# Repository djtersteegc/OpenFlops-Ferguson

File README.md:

This is a respin of [SukkoPera's](https://github.com/SukkoPera) original [OpenFlops](https://github.com/SukkoPera/OpenFlops) project to create a custom version that plugs directly into the male 50 pin disk header of my [Ferguson Big Board](https://github.com/djtersteegc/Ferguson-Big-Board-Reproduction) SBC Z80 computer.  Changes from the original version include:

- Updated to KiCad 7.x
- Switched from USB to Micro SD for image storage
- Switched to 74LS07's for buffers
- Interface is a now a 50 pin connector and PCB laid out specifically for the Ferguson use case

Version 1.1 shrinks the SWD pin headers to allow room for a 9mm speaker to make floppy'ish sounds when accessing and seeking.

https://youtu.be/Bbqj_xtnAqc

Schematic v1.0 - https://djtersteegc.github.io/OpenFlops-Ferguson/OpenFlops-Ferguson-Schematic-v1.0.pdf

Schematic v1.1 - https://djtersteegc.github.io/OpenFlops-Ferguson/OpenFlops-Ferguson-Schematic-v1.1.pdf

### BOM

Interactive v1.0 - [https://djtersteegc.github.io/OpenFlops-Ferguson/ibom-v1.0.html](https://djtersteegc.github.io/OpenFlops-Ferguson/ibom-v1.0.html)

CSV v1.0 - [https://djtersteegc.github.io/OpenFlops-Ferguson/OpenFlops-Ferguson-BOM-v1.0.csv](https://djtersteegc.github.io/OpenFlops-Ferguson/OpenFlops-Ferguson-BOM-v1.0.csv)

Interactive v1.1 - [https://djtersteegc.github.io/OpenFlops-Ferguson/ibom-v1.1.html](https://djtersteegc.github.io/OpenFlops-Ferguson/ibom-v1.1.html)

CSV v1.1 - [https://djtersteegc.github.io/OpenFlops-Ferguson/OpenFlops-Ferguson-BOM-v1.1.csv](https://djtersteegc.github.io/OpenFlops-Ferguson/OpenFlops-Ferguson-BOM-v1.1.csv)

For the MCU I switched from the STM32F105RBT6 to the Artery AT32F435RGT7 which is now well supported by FlashFloppy and a more capable chip for potential future expansion (dual drives?). You could also build with the STM32F105RBT6 and use the appropiate STM programmer and FlashFloppy firmware version.

C12 is a extra bulk capacitor footprint I added near the MCU in case it was needed.  I've run mine without and seems fine, so can be considered optional.  Measured current draw on the board is around 100ma, with the OLED display active.

### Assembly

Do all the SMD components first using your favorite method.  I tried the Proto-Advantage PA0096-S TQFP-64 stencil for the MCU since I didn't have another one anywhere and was to cheap to get a proper stencil from JLCPCB, but unfortunately the pads are 2mm in length on that guy which result in excessive solder paste being applied to the board and then general sadness and bridging after it reflows.

I would flash the MCU (see below) next either by soldering on the angle headers for the SWD port or just holding headers in the holes to ensure everything works before doing the rest of the through hole components since it's a whole lot easier to do rework if needed with nothing else on the board.

Once all flashed and assembled, the normal jumper settings for the BOOT0 and BOOT1 pins are to the left (connected to GND).  BOOT1 really isn't even needed, but I added it just in case.

### Firmware Flashing

To flash the FlashFloppy firmware on the MCU, I used Arterty's AT-Link+ hooked up the SWD port on the board.

For the v1.1 boards, a pogo pin clamp is handy.

If your MCU is blank, you should be able to connect without having to set the BOOT0 jumper to high (3.3V)  If not and it is already running a user flashed program, you will need to move BOOT0 to the right in order for the bootloader to run and you can connect for flashing.

Using Artery's ICP Programmer, **Connect** to the MCU and load the appropiate FlashFloppy hex file via the **Add** button and then hit **DownLoad**.

Move the BOOT0 jumper back to the left (GND, logical 0) if needed and once you repower, the OLED should display FlashFloppy+. 

### Usage

If you have v1.0 repoduction board (or original), you will need to add a bodge wire to pull 5V power from the resistor network to either pin 4, 6, or 8 (or all three) since the FlashFloppy board is powered directly from normally unused pins on the Ferguson's floppy port.

If you have a version 1.1 board, simply close the solder jumper on the back of the board to do the same.

Plug into your Ferguson and enjoy a clutter free floppy experience. ;)

### Versions

**v1.0** - Initial release, tested and working.

**v1.1** - Shrinks the SWD pin headers to allow room for a 9mm speaker.

### Getting a Board

If you're in the US, hit me up on this VCFed thread and if I have any extras, can drop one in the mail for a couple bucks.  

https://forum.vcfed.org/index.php?threads/recreating-the-ferguson-big-board.68349/

Otherwise [gerbers](gerbers) are available for use at your favorite PCB fab. 

### License

The OpenFlops documentation, including the design itself, is copyright &copy; SukkoPera 2019-2020.

OpenFlops is Open Hardware licensed under the [CERN OHL v. 1.2](http://ohwr.org/cernohl).

You may redistribute and modify this documentation under the terms of the CERN OHL v.1.2. This documentation is distributed *as is* and WITHOUT ANY EXPRESS OR IMPLIED WARRANTIES whatsoever with respect to its functionality, operability or use, including, without limitation, any implied warranties OF MERCHANTABILITY, SATISFACTORY QUALITY, FITNESS FOR A PARTICULAR PURPOSE or infringement. We expressly disclaim any liability whatsoever for any direct, indirect, consequential, incidental or special damages, including, without limitation, lost revenues, lost profits, losses resulting from business interruption or loss of data, regardless of the form of action or legal theory under which the liability may be asserted, even if advised of the possibility or likelihood of such damages.

A copy of the full license is included in file [LICENSE.pdf](LICENSE.pdf), please refer to it for applicable conditions. In order to properly deal with its terms, please see file [LICENSE_HOWTO.pdf](LICENSE_HOWTO.pdf).

The contact points for information about manufactured Products (see section 4.2) are listed in file [PRODUCT.md](PRODUCT.md).

Any modifications made by Licensees (see section 3.4.b) shall be recorded in file [CHANGES.md](CHANGES.md).

The Documentation Location of the original project is https://github.com/SukkoPera/OpenFlops/.

### Thanks
- SukkoPera for the [OpenFlops](https://github.com/SukkoPera/OpenFlops) project
- H.M for publishing the [original Gotek schematics](docs/gotek_usb-fde_block-diagram.jpg)
- [keirf](https://github.com/keirf) for FlashFloppy

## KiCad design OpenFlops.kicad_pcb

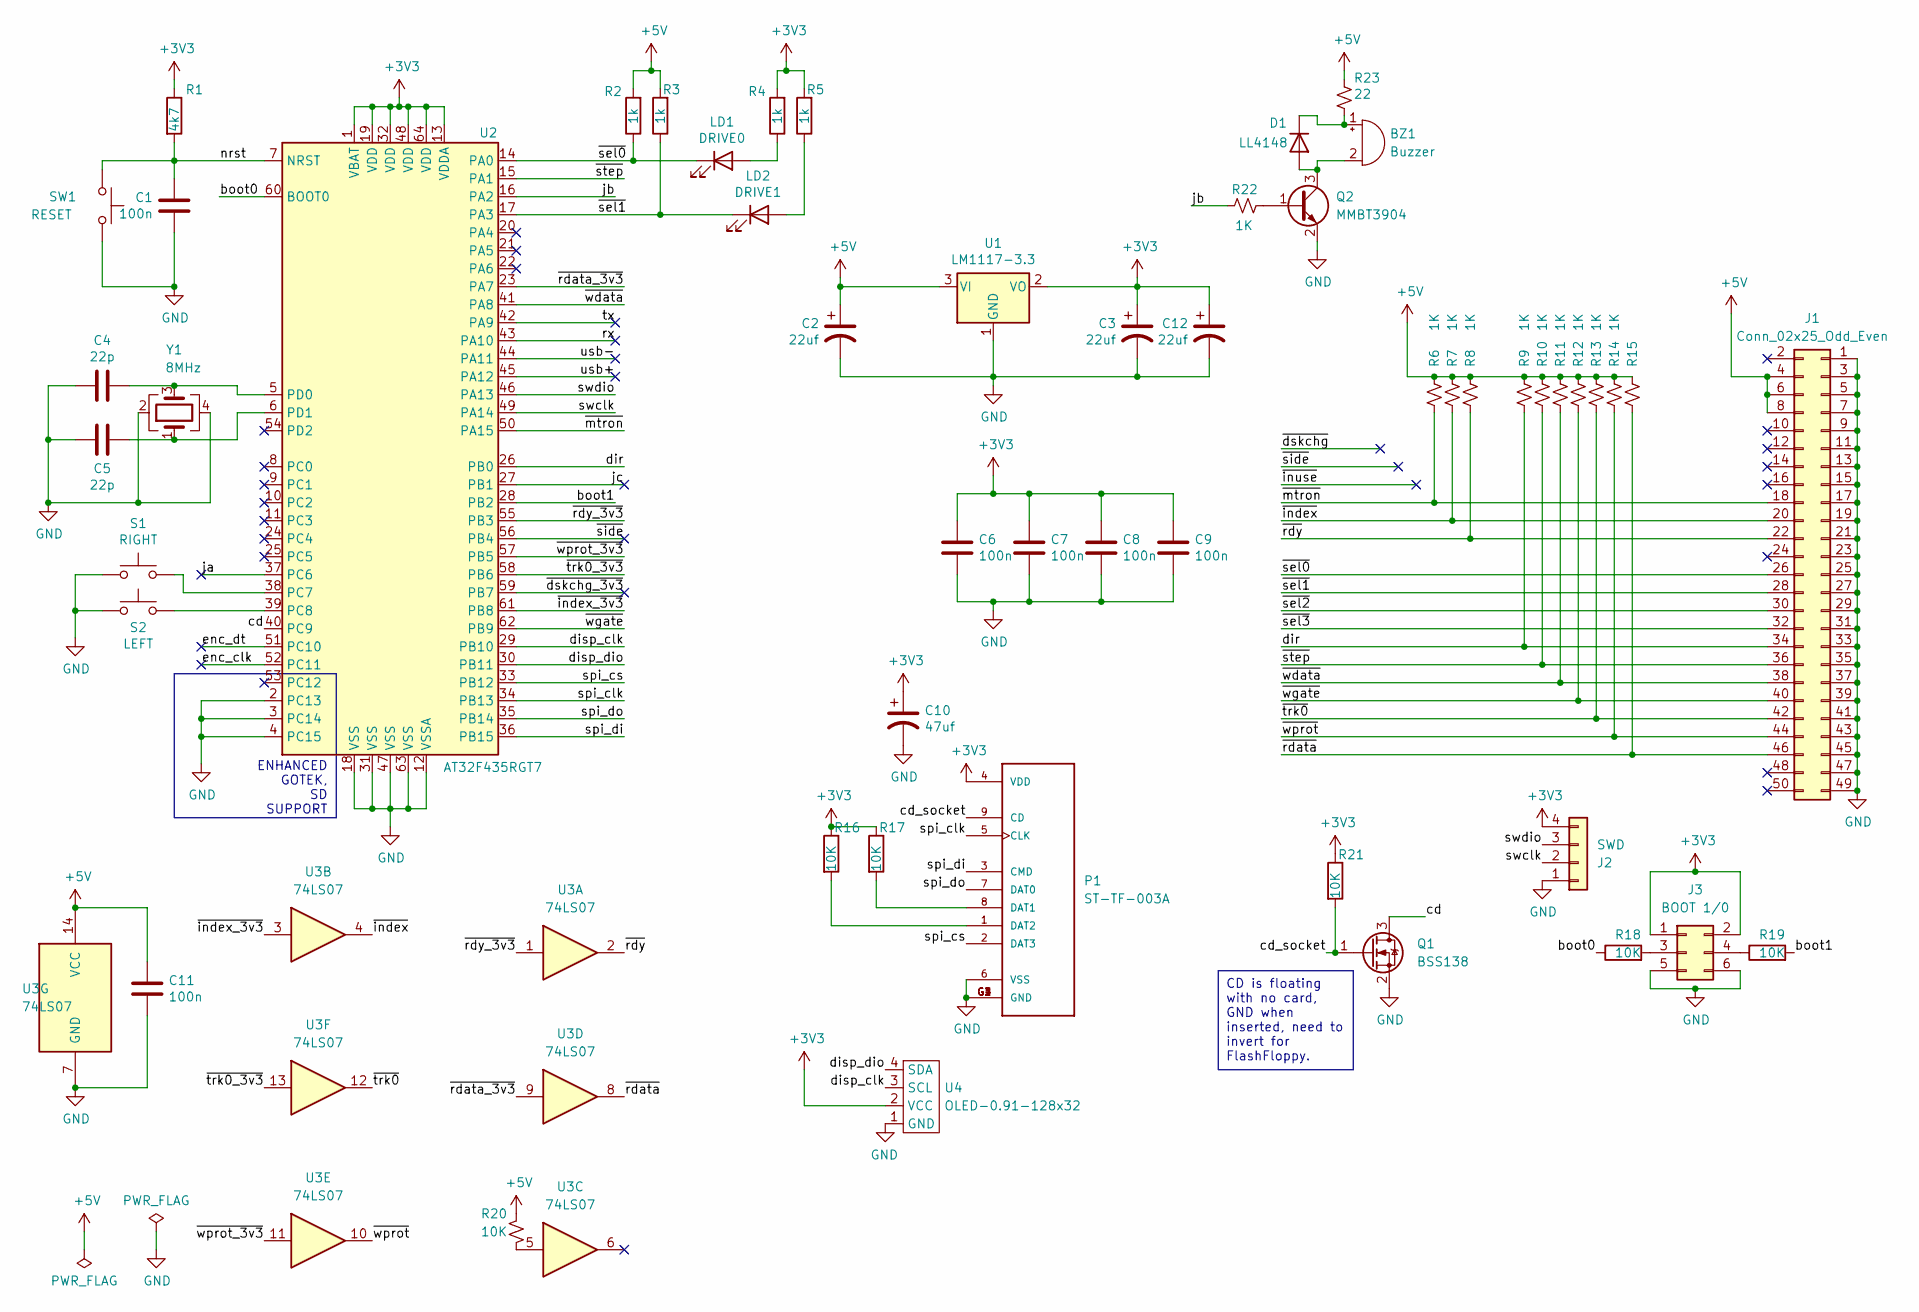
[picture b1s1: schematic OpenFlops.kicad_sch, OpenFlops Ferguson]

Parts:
BZ1: Buzzer; MagneticBuzzer_PUI_AT-0927-TT-6-R
C1, C6, C7, C8, C9, C11: 100n; C_0805_2012Metric; MFG Part Num MULTILAYER CERAMIC CAPACITORS MLCC - SM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; JLCPCB PN CC0805KRX7R9BB104
C2, C3, C12: 22uf; CP_EIA-3216-12_Kemet-S_Pad1.58x1.35mm_HandSolder
C4, C5: 22p; C_0805_2012Metric; MFG Part Num MULTILAYER CERAMIC CAPACITORS MLCC - SM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; JLCPCB PN CL21C220JBANNNC
C10: 47uf; CP_EIA-3528-12_Kemet-T_Pad1.50x2.35mm_HandSolder
D1: LL4148; D_MiniMELF
J1: Conn_02x25_Odd_Even; PinSocket_2x25_P2.54mm_Vertical
J2: SWD; PinHeader_1x04_P2.54mm_Vertical
J3: BOOT 1/0; PinHeader_2x03_P2.00mm_Vertical
LD1: DRIVE0; LED_D3.0mm
LD2: DRIVE1; LED_D3.0mm
P1: ST-TF-003A; SUNTECH_ST-TF-003A
Q1: BSS138; SOT-23
Q2: MMBT3904; SOT-23
R1: 4k7; R_0805_2012Metric; MFG Part Num CHIP RESISTOR - SURFACE MOUNT 4.7KOHMS 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; JLCPCB PN 0805W8F4701T5E
R2, R3: 1k; R_0805_2012Metric; MFG Part Num CHIP RESISTOR - SURFACE MOUNT 1KOHMS ±1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; JLCPCB PN 0805W8F1001T5E
R4, R5: 1k; R_0805_2012Metric
R6, R7, R8, R9, R10, R11, R12, R13, R14, R15, R22: 1K; R_0805_2012Metric
R16, R17, R18, R19, R21: 10K; R_0805_2012Metric; MFG Part Num CHIP RESISTOR - SURFACE MOUNT 4.7KOHMS 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; JLCPCB PN 0805W8F4701T5E
R20: 10K; R_0805_2012Metric
R23: 22; R_0805_2012Metric
S1: RIGHT; PUSH_BUTTON_RIGHT_ANGLE
S2: LEFT; PUSH_BUTTON_RIGHT_ANGLE
SW1: RESET; SW_Push_SPST_NO_Alps_SKRK
U1: LM1117-3.3; SOT-223-3_TabPin2; MFG Part Num LOW DROPOUT REGULATORS(LDO) POSITIVE FI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; JLCPCB PN AMS1117-3.3
U2: AT32F435RGT7; LQFP-64_10x10mm_P0.5mm; MFG Part Num ST MICROELECTRONICS LQFP-64_10X10X05P R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; JLCPCB PN STM32F105RBT6
U3: 74LS07; SOIC-14_3.9x8.7mm_P1.27mm
U4: OLED-0.91-128x32
Y1: 8MHz; Crystal_SMD_Abracon_ABM8G-4Pin_3.2x2.5mm

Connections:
+3V3: C3.1, C6.1, C7.1, C8.1, C9.1, C10.1, C12.1, J2.4, J3.1, J3.2, P1.4 (VDD), R1.1, R4.2, R5.2, R16.1, R17.1, R21.1, U1.2 (VO), U2.1 (VBAT), U2.13 (VDDA), U2.19 (VDD), U2.32 (VDD), U2.48 (VDD), U2.64 (VDD), U4.2 (VCC)
+5V: C2.1, C11.1, J1.4, J1.6, J1.8, R2.2, R3.2, R6.1, R7.1, R8.1, R9.1, R10.1, R11.1, R12.1, R13.1, R14.1, R15.1, R20.1, R23.1, U1.3 (VI), U3.14 (VCC)
/boot0: R18.1, U2.60 (BOOT0)
/boot1: R19.2, U2.28 (PB2)
/cd: Q1.3 (D), U2.40 (PC9)
/cd_socket: P1.9 (CD), Q1.1 (G), R21.2
/dir: J1.34, R9.2, U2.26 (PB0)
/disp_clk: U2.29 (PB10), U4.3 (SCL)
/disp_dio: U2.30 (PB11), U4.4 (SDA)
/enc_clk: U2.52 (PC11)
/enc_dt: U2.51 (PC10)
/ja: U2.37 (PC6)
/jb: R22.2, U2.16 (PA2)
/jc: U2.27 (PB1)
/nrst: C1.1, R1.2, SW1.1, U2.7 (NRST)
/rx: U2.43 (PA10)
/spi_clk: P1.5 (CLK), U2.34 (PB13)
/spi_cs: P1.2 (DAT3), U2.33 (PB12)
/spi_di: P1.3 (CMD), U2.36 (PB15)
/spi_do: P1.7 (DAT0), U2.35 (PB14)
/swclk: J2.2, U2.49 (PA14)
/swdio: J2.3, U2.46 (PA13)
/tx: U2.42 (PA9)
/usb+: U2.45 (PA12)
/usb-: U2.44 (PA11)
/~dskchg_3v3: U2.59 (PB7)
/~index_3v3: U2.61 (PB8), U3.3
/~index: J1.20, R7.2, U3.4
/~mtron: J1.18, R6.2, U2.50 (PA15)
/~rdata_3v3: U2.23 (PA7), U3.9
/~rdata: J1.46, R15.2, U3.8
/~rdy_3v3: U2.55 (PB3), U3.1
/~rdy: J1.22, R8.2, U3.2
/~sel0: J1.26, LD1.1 (K), R2.1, U2.14 (PA0)
/~sel1: J1.28, LD2.1 (K), R3.1, U2.17 (PA3)
/~sel2: J1.30
/~sel3: J1.32
/~side: U2.56 (PB4)
/~step: J1.36, R10.2, U2.15 (PA1)
/~trk0_3v3: U2.58 (PB6), U3.13
/~trk0: J1.42, R13.2, U3.12
/~wdata: J1.38, R11.2, U2.41 (PA8)
/~wgate: J1.40, R12.2, U2.62 (PB9)
/~wprot_3v3: U2.57 (PB5), U3.11
/~wprot: J1.44, R14.2, U3.10
GND: C1.2, C2.2, C3.2, C4.2, C5.2, C6.2, C7.2, C8.2, C9.2, C10.2, C11.2, C12.2, J1.1, J1.3, J1.5, J1.7, J1.9, J1.11, J1.13, J1.15, J1.17, J1.19, J1.21, J1.23, J1.25, J1.27, J1.29, J1.31, J1.33, J1.35, J1.37, J1.39, J1.41, J1.43, J1.45, J1.47, J1.49, J2.1, J3.5, J3.6, P1.6 (VSS), P1.G1 (GND), P1.G2 (GND), P1.G3 (GND), P1.G4 (GND), Q1.2 (S), Q2.2 (E), S1.1, S2.1, SW1.2, U1.1 (GND), U2.2 (PC13), U2.3 (PC14), U2.4 (PC15), U2.12 (VSSA), U2.18 (VSS), U2.31 (VSS), U2.47 (VSS), U2.63 (VSS), U3.7 (GND), U4.1 (GND), Y1.2, Y1.4
unnamed: BZ1.1 (+), D1.1 (K), R23.2
unnamed: BZ1.2 (-), D1.2 (A), Q2.3 (C)
unnamed: J3.3, R18.2
unnamed: J3.4, R19.1
unnamed: LD1.2 (A), R4.1
unnamed: LD2.2 (A), R5.1
unnamed: P1.8 (DAT1), R17.2
unnamed: P1.1 (DAT2), R16.2
unnamed: Q2.1 (B), R22.1
unnamed: R20.2, U3.5
unnamed: S1.2, U2.38 (PC7)
unnamed: S2.2, U2.39 (PC8)
unnamed: C4.1, U2.5 (PD0), Y1.3
unnamed: C5.1, U2.6 (PD1), Y1.1

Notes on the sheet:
CD is floating with no card, GND when inserted, need to invert for FlashFloppy.
ENHANCED GOTEK, SD SUPPORT

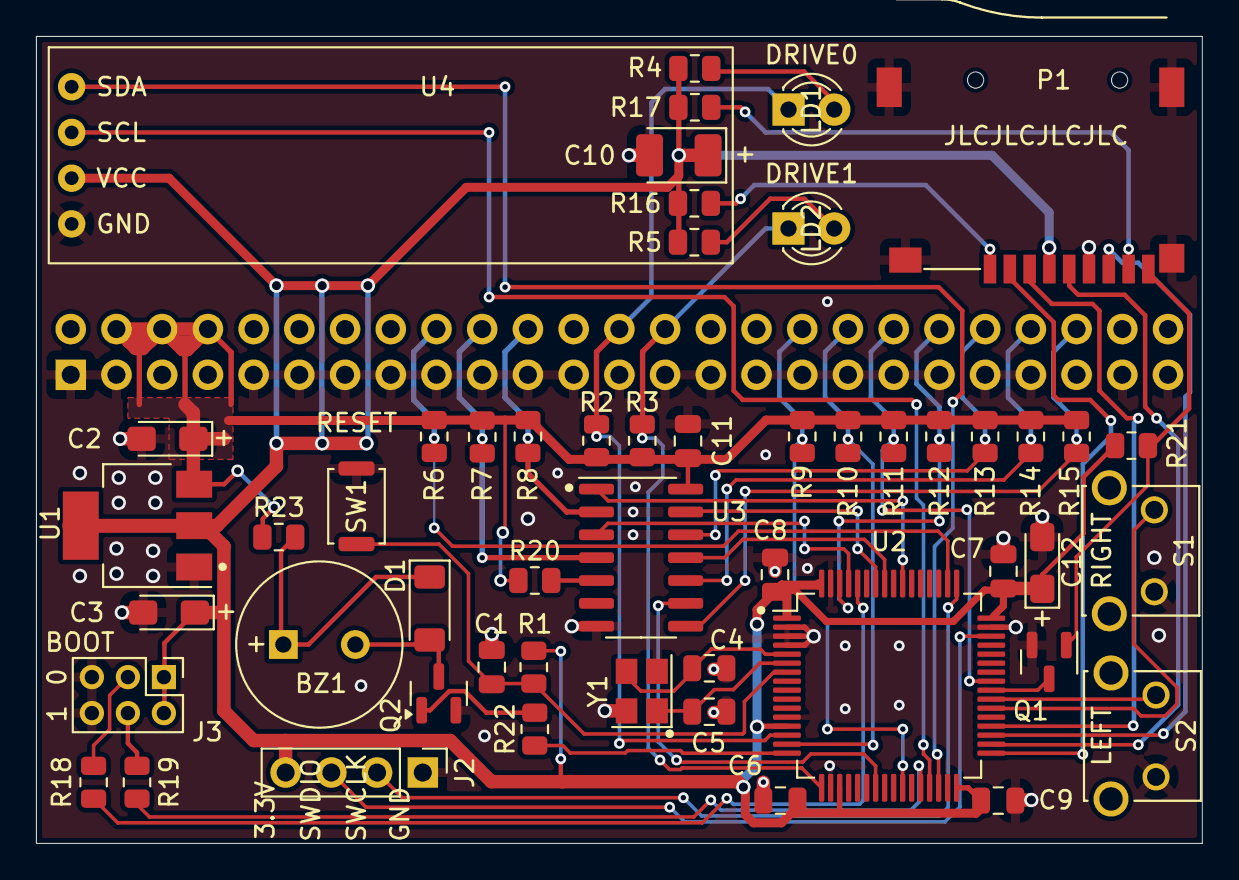
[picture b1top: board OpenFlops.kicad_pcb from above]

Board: 2 copper layers, 64.8 x 44.8 mm, 53 parts (1 on the bottom side), 48 nets.

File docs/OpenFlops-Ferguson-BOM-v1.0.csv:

"#","Reference","Qty","Value","Footprint","DNP"
"1","C1, C6, C7, C8, C9, C11","6","100n","Capacitor_SMD:C_0805_2012Metric",""
"2","C2, C3, C12","3","22uf","Capacitor_Tantalum_SMD:CP_EIA-3216-12_Kemet-S_Pad1.58x1.35mm_HandSolder",""
"3","C4, C5","2","22p","Capacitor_SMD:C_0805_2012Metric",""
"4","C10","1","47uf","Capacitor_Tantalum_SMD:CP_EIA-3528-12_Kemet-T_Pad1.50x2.35mm_HandSolder",""
"5","J1","1","Conn_02x25_Odd_Even","Connector_PinSocket_2.54mm:PinSocket_2x25_P2.54mm_Vertical",""
"6","J2","1","SWD","Connector_PinHeader_2.54mm:PinHeader_1x04_P2.54mm_Horizontal",""
"7","J3","1","BOOT 1/0","Connector_PinHeader_2.00mm:PinHeader_2x03_P2.00mm_Vertical",""
"8","LD1","1","DRIVE0","LED_THT:LED_D3.0mm",""
"9","LD2","1","DRIVE1","LED_THT:LED_D3.0mm",""
"10","P1","1","ST-TF-003A","ST-TF-003A:SUNTECH_ST-TF-003A",""
"11","Q1","1","BSS138","Package_TO_SOT_SMD:SOT-23",""
"12","R1","1","4k7","Resistor_SMD:R_0805_2012Metric",""
"13","R2, R3, R4, R5","4","1k","Resistor_SMD:R_0805_2012Metric",""
"14","R6, R7, R8, R9, R10, R11, R12, R13, R14, R15","10","1K","Resistor_SMD:R_0805_2012Metric",""
"15","R16, R17, R18, R19, R20, R21","6","10K","Resistor_SMD:R_0805_2012Metric",""
"16","S1","1","RIGHT","OpenFlops:PUSH_BUTTON_RIGHT_ANGLE",""
"17","S2","1","LEFT","OpenFlops:PUSH_BUTTON_RIGHT_ANGLE",""
"18","SW1","1","RESET","Button_Switch_SMD:SW_Push_SPST_NO_Alps_SKRK",""
"19","U1","1","LM1117-3.3","Package_TO_SOT_SMD:SOT-223-3_TabPin2",""
"20","U2","1","AT32F435RGT7","Package_QFP:LQFP-64_10x10mm_P0.5mm",""
"21","U3","1","74LS07","Package_SO:SOIC-14_3.9x8.7mm_P1.27mm",""
"22","U4","1","OLED-0.91-128x32","Tersteeg:OLED-0.91-128x32",""
"23","Y1","1","8MHz","Crystal:Crystal_SMD_Abracon_ABM8G-4Pin_3.2x2.5mm",""

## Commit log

2024-01-23 Restructure for v1.0 or the Ferguson version
2025-02-23 Add v1.1 schematic and CSV BOM
2025-02-23 Update docs
2025-02-23 Fix Schematic PDF

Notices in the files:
OpenFlops.kicad_pcb:
Licensed under CERN OHL v.1.2
